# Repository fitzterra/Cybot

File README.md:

Cybot Resurrected
=================

**Table of Contents**
1. [Features](#features)
2. [Hardware and Electronics](#hardware-and-electronics)
3. [Software](#software)

----

This is a project to bring my old [Cybot] back my to life.

</img>
</img>

After I lost my remote control (it was stolen actually, by some idiot who
probably thought it was a game controller :angry: ), Cybot has just been sitting
there for quite a number of years.

A while back I built [FoamBot] which was a robot in which I used [Foam Board]
exclusively as construction material, continues servos as drive train, and an
Arduino Uno as MCU. The software for [FoamBot] was based on a simple
[co-operative multitasking] library, with all functionality built as (almost)
completely independent tasks to form a very loosely defined type of Robot
Operating System.

Due to time constraints and some waning of interest, FoamBot took a backseat.
When I now recently got the urge to build a remote controller robot again, I
decided to use as much of Cybot as possible, but replace the MCU with something
Arduino based. This is where we now begin :smile:.

Features
--------
This list will be expanded as more things are added, at a minimum, these are the
features I would like for now:

* Use as much of the Cybot sensors and hardware as possible
* Controlled via:
    - Direct serial connection - this will be more for testing and debugging,
      and will be a tethered connection.
    - Infrared - this will obviously be a remote control, it should use the
      original Cybot IR Receiver, and should be able to use any available IR
      remote (after training Cybot for the remote - see below)
    - Bluetooth - also a remote control. This will allow many mobile apps to act
      as a remote control, and will allow things like using a phone's gyro,
      accelerometer and other sensors to control the bot by simply tilting and
      moving the phone in the air.
* All input controls should have the options to be trainable in order to ensure
  the controller can issue the correct robot control commands. Trained control
  mappings should be stored in EEPROM to survive power offs.
* Obstacle avoidance using light sensors and/or ultrasonic and/or IR (using a
  separate IR sensor).
* Line follower option.

Hardware and Electronics
------------------------
ToDo

Software
--------
See [here](firmware) for details about the Robot Control software.

[Cybot]: https://en.wikipedia.org/wiki/Real_Robots
[FoamBot]: https://github.com/fitzterra/FoamBot
[Foam Board]: https://en.wikipedia.org/wiki/Foamcore
[co-operative multitasking]: https://github.com/fitzterra/Task
[firmware]: firmware/README.md

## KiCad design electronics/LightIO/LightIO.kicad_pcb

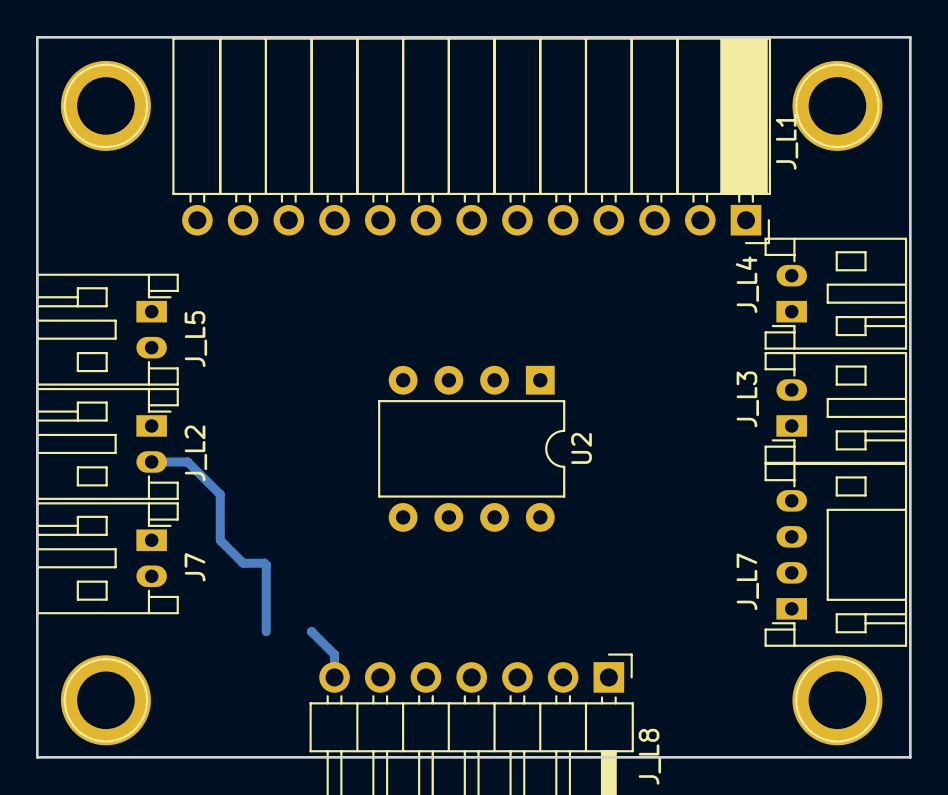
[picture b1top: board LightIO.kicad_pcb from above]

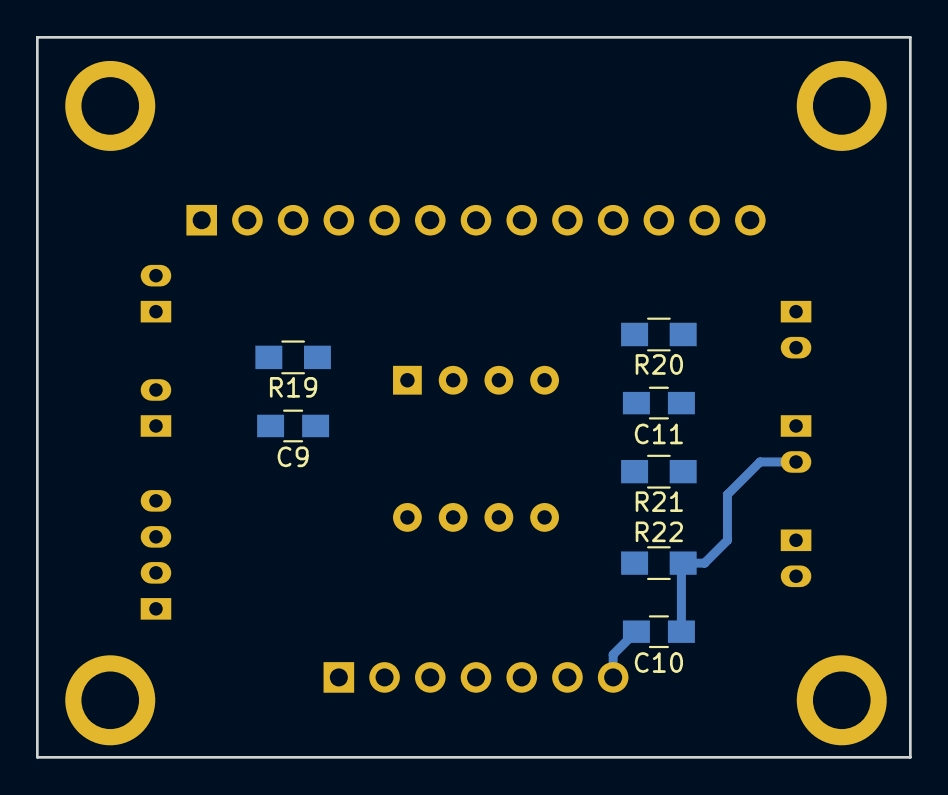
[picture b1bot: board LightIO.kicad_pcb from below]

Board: 2 copper layers, 48.5 x 40.0 mm, 16 parts (7 on the bottom side), 19 nets.

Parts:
C9, C10, C11: 100nF; C_0805_HandSoldering
J7: Piezo; JST_PH_S2B-PH-K_02x2.00mm_Angled
J_L1: LightProcPCB; Socket_Strip_Angled_1x13_Pitch2.54mm
J_L2: CDS-L; JST_PH_S2B-PH-K_02x2.00mm_Angled
J_L3: CDS-R; JST_PH_S2B-PH-K_02x2.00mm_Angled
J_L4: LED-R; JST_PH_S2B-PH-K_02x2.00mm_Angled
J_L5: LED-L; JST_PH_S2B-PH-K_02x2.00mm_Angled
J_L7: Line; JST_PH_S4B-PH-K_04x2.00mm_Angled
J_L8: Motor PCB; Pin_Header_Angled_1x07_Pitch2.54mm
R19: 47k; R_0805_HandSoldering
R20: 62; R_0805_HandSoldering
R21, R22: 300; R_0805_HandSoldering
U2: LM311; DIP-8_W7.62mm

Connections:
/+5V: C9.1, J_L1.11, J_L2.1, J_L3.1, J_L7.4, J_L8.5, R19.2, U2.8
/+6V: J_L1.12, J_L8.6, R20.2
/AntLED: J_L1.6, J_L4.2
/BZ+: J7.1, J_L1.2
/BZ-: J7.2, J_L1.3
/CDS-L: J_L1.4, R22.1
/CDS-R: J_L1.5, R21.2
/LnFol: J_L1.1, R19.1, U2.7
/M1A: J_L1.9, J_L8.3
/M1B: J_L1.10, J_L8.4
/M2A: J_L1.7, J_L8.1
/M2B: J_L1.8, J_L8.2
GND: C9.2, C10.2, C11.2, J_L1.13, J_L7.1, J_L8.7, U2.1, U2.4
unnamed: C10.1, J_L2.2, R22.2
unnamed: C11.1, J_L3.2, R21.1
unnamed: J_L4.1, J_L5.2
unnamed: J_L5.1, R20.1
unnamed: J_L7.2, U2.3
unnamed: J_L7.3, U2.2

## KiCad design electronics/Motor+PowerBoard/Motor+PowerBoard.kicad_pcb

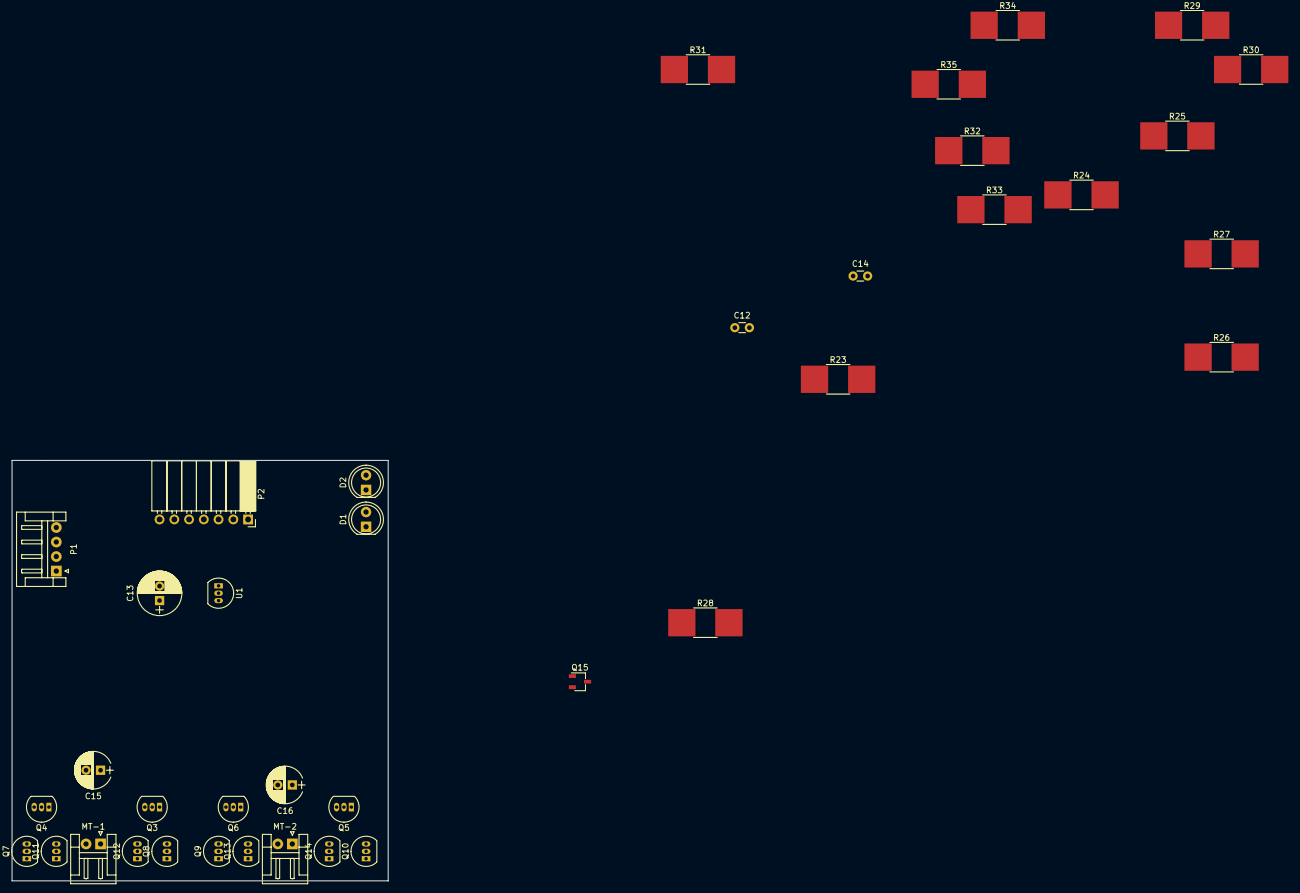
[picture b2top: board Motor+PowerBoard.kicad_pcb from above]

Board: 2 copper layers, 64.8 x 72.4 mm, 38 parts (0 on the bottom side), 32 nets, no tracks yet.

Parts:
C12, C14: 100nF; C_Disc_D3.0mm_W1.6mm_P2.50mm
C13: 220uF; CP_Radial_D7.5mm_P2.50mm
C15, C16: 10uF; CP_Radial_D6.3mm_P2.50mm
D1: Red; LED_D5.0mm
D2: Green; LED_D5.0mm
MT-1, MT-2: JSTx2; JST_EH_S02B-EH_02x2.50mm_Angled
P1: Power; JST_EH_S04B-EH_04x2.50mm_Angled
P2: Connect; Socket_Strip_Angled_1x07_Pitch2.54mm
Q3, Q4, Q5, Q6: S8050; TO-92_Inline_Narrow_Oval
Q7, Q8, Q9, Q10: 2SC3279; TO-92_Inline_Narrow_Oval
Q11, Q12, Q13, Q14: 2SA1300; TO-92_Inline_Narrow_Oval
Q15: NPN SMD; TSOT-23
R23: 10; R_2816_HandSoldering
R24, R25: 2k7; R_2816_HandSoldering
R26: 10k; R_2816_HandSoldering
R27: 1k2; R_2816_HandSoldering
R28, R29, R30, R31: 1k; R_2816_HandSoldering
R32, R33, R34, R35: 100; R_2816_HandSoldering
U1: LM78L05_TO92; TO-92_Inline_Narrow_Oval

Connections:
+6V: C12.1, P2.6, Q11.1, Q12.1, Q13.1, Q14.1
+9V: R23.2, R24.2, R25.2, R26.2
/+5V: C14.1, P2.5, U1.1
/M1A: P2.3, R29.1
/M1B: P2.4, R28.1
/M2A: P2.1, R30.1
/M2B: P2.2, R31.1
GND: C12.2, C13.2, C14.2, D1.1, D2.1, P2.7, Q7.1, Q8.1, Q9.1, Q10.1, Q15.3, R27.1, U1.2
unnamed: C13.1, R23.1, U1.3
unnamed: C15.1, Q7.2, Q11.2
unnamed: C15.2, Q8.2, Q12.2
unnamed: C16.1, Q9.2, Q13.2
unnamed: C16.2, Q10.2, Q14.2
unnamed: D1.2, Q15.2, R25.1
unnamed: D2.2, R24.1
unnamed: Q3.1, Q8.3
unnamed: Q3.2, R28.2
unnamed: Q3.3, R33.2
unnamed: Q4.1, Q7.3
unnamed: Q4.2, R29.2
unnamed: Q4.3, R32.2
unnamed: Q5.2, R31.2
unnamed: Q5.3, R34.2
unnamed: Q6.1, Q9.3
unnamed: Q6.2, R30.2
unnamed: Q6.3, R35.2
unnamed: Q5.1, Q10.3
unnamed: Q11.3, R33.1
unnamed: Q12.3, R32.1
unnamed: Q13.3, R34.1
unnamed: Q14.3, R35.1
unnamed: Q15.1, R26.1, R27.2

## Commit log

2017-09-03 Initial commit.
2017-09-03 Add License
2017-09-06 Initial documentation
2017-09-07 Add low level wheel control
    The WheelXXX classes are used to control a rotation direction and speed
    of a single wheel. The wheel can be driven by a Continues Rotation Servo
    or be a Brushed DC Motor driven via an HBRidge.
    The Wheel object abstracts the rotation control such that the actual
    drive mechanism is irrelevant.
    Speed is managed as a percentage of full speed, i.e. a speed value of
2017-09-10 Add movement control via the DriveTrain class.
    The DriveTrain combines two wheels into on drive train, allowing moving
    and turning of the robot.
    Include visuals to illustrate control of movement w.r.t. speed and
    direction settings.
    Add tests to test drive train functionality.
    Update documentation with details about the drive train and movement
2017-09-12 First test of Cybot firmware
    This is the first test of combining the various modules into one sketch
    to create the Cybot firmware.
    The DriveTrain was changed to make it a Task which will check for any new
    commands that it needs to action, and issue the required changes to the
    Wheels.
    Some minor comment changes is to start bringing Class, method and
2017-09-14 Setup up software serial port (SSerial) for Bluetooth
    The Bluetooth input method used to directly connect to, and set up, it's
    own software serial port for input only. Since this port was only
    available inside the BT input handler, it was not easy to use the BT
    port for general output too, without hooking this into the BT input
    handler.
    By creating a generic Software Serial port, called SSerial, set up and
2017-09-15 Speed/Direction feedback over Bluetooth. Control improvement. Bug fixes.
    * Add an option to feed speed and direction values back to Bluetooth
    controller in DriveTrain if the BT_FEEDBACK option is enabled in
    config.h
    * Control improvements to give a more natural control experience:
    * The forward command will now set the direction to 0 and make sure
    the speed is set for forward (positive) at the current speed.
2017-09-15 Add optional power start function for DC motors.
    Using PWM speed control for a DC motor makes getting the motor into
    motion at slow speeds a bit difficult at times. The power start
    functionality allows for a DC motor put into motion from stand still, to
    be ramped up to full power to start the motion, and then tapering the
    speed down to the desired start speed over a short period of time
    (milliseconds, normally).
2017-09-20 Fix Serial and BT learn modes to use Serial output and not debug marco.
2017-09-30 Start of extended serial input feature
    This branch will be used to allow the serial input methods to accept
    extended input instead of only single characters.
    This will make it possible to send commands like `d20` to set the
    direction to the value 20, or `s-80` to set the speed to -80, etc.
2017-09-30 Add global shared space. Fix slice hogging by DriveTrain task.
    * Add a global data structure consiting of variables for holding various
    state information. This structure is globally available by any module
    that includes config.h and allows easy, but structured sharing of
    global data between modules and tasks.
    * Fix the canRun() method of DriveTrain so that it only runs for new
    commands in can hanlde. The way that the TaskSchedular works, is that
2017-10-05 Add support for 128x64 SSD1306 type OLED over I2C.
    First phase support for adding a display. Only the OLED display above is
    supported for now.
2017-10-05 First add of some schematics in KiCAD format.
    These are a bit of a jumble of some of the Cybot schematics reproduced,
    and then the start of schematics for re-using the current hardware with
    an Arduino.
    Still a work in progress.
2017-10-14 WIP: crash bug to be found and fixed still
    The code crashes the mcu and I'm not sure where the problem is yet.
    Seems it may be related to memory, so just comitting what I have so far
    on this branch so I can go back to a working version and start doing
    some memory profiling to get an idea of memory usage on the working
    version.
    Will then come bcak here to do the same profiling and see if it changes
2019-05-14 Create May_be_of_Intrest
    Information on how I converted my Cybot
